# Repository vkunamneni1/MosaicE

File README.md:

# MosaicE
MosaicE is a PCB controller board that's powered by a XIAO RP2040, three buttons, a rotary encoder, and four LEDs. There are 3 modes: clock, binary counter, and gradient light mode. All modes are controlled by user input through the buttons and knob, and are all programmed in C++ (Arduino code).

## Modes
1. ***Clock*** - 1 LED blinks to acknowledge mode change. Then 3 LEDs act as an hour counter, minute counter, and second counter, all blinking when their counted time has elapsed.
2. ***Binary*** - 1 LED blinks to acknowledge mode change. Then the 4 LEDs act as a binary counter, counting up from 0000 to 1111. This repeats.
3. ***Gradient Light Mode*** - 1 LED blinks to acknowledge mode change. Then, the rotary encoder (knob) acts as a controller for all 4 LEDs. The more you turn it clockwise, the more LEDs that light up.
4. ***Stop*** - All LEDs blink to acknowledge that the stop button has been pressed. Essentially, it stops all mode functions.

## 3D Model

(models found on the GrabCAD Library and combined in KiCad)

## PCB Design

(made in KiCad)

## Schematic

(made in KiCad)

## Firmware
Source files can be found in the firmware directory. It was made in the Arduino IDE, using third-party libraries such as RotaryEncoder by Matthias Hertel.

##### made for Pathfinder

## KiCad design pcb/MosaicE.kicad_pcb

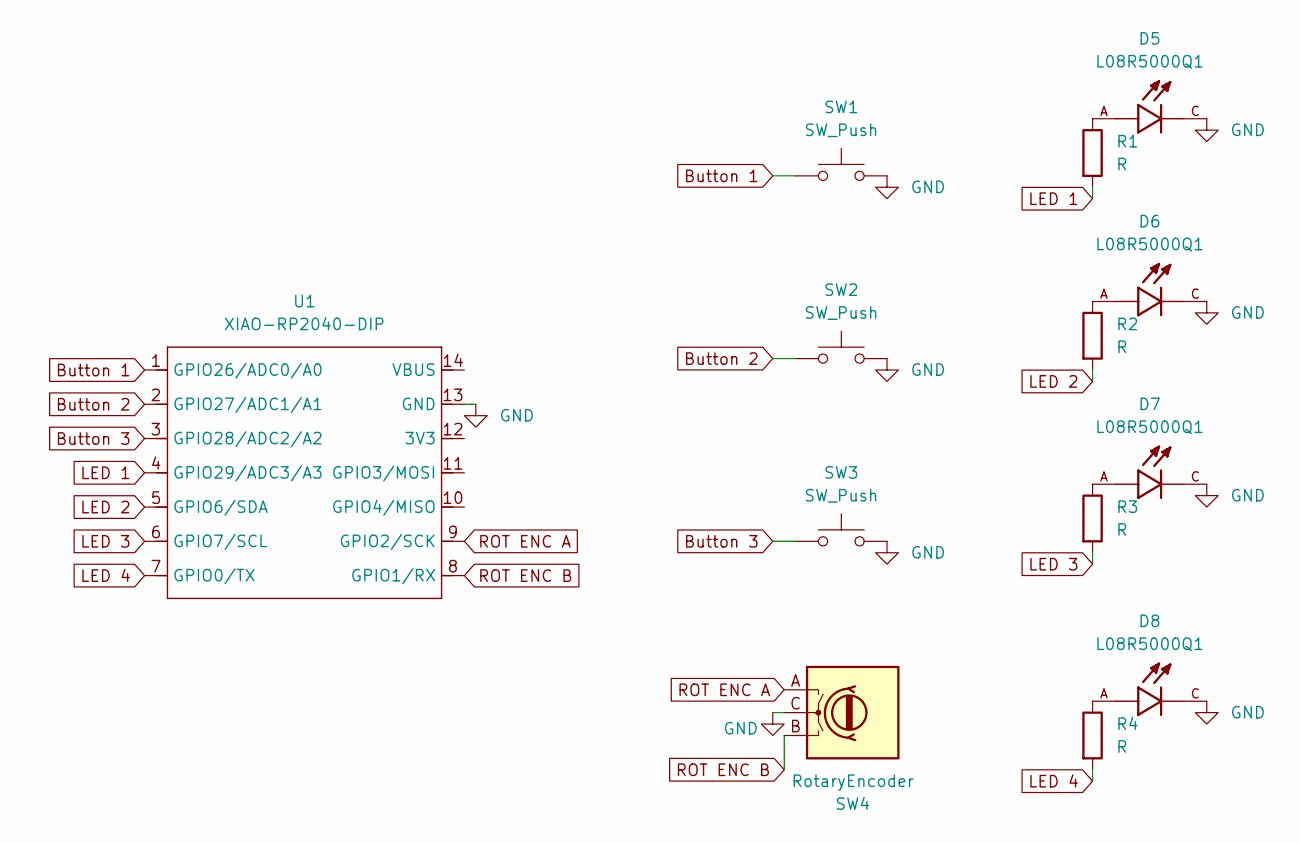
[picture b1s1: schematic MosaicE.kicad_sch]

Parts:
D5, D6, D7, D8: L08R5000Q1; LEDRD254W57D500H1070; PARTREV NA
R1, R2, R3, R4: R; R_Axial_DIN0204_L3.6mm_D1.6mm_P5.08mm_Horizontal
SW1, SW2, SW3: SW_Push; SW_Cherry_MX_1.00u_PCB
SW4: RotaryEncoder; RotaryEncoder_Alps_EC11E_Vertical_H20mm
U1: XIAO-RP2040-DIP

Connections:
Button 1: SW1.1, U1.1 (GPIO26/ADC0/A0)
Button 2: SW2.1, U1.2 (GPIO27/ADC1/A1)
Button 3: SW3.1, U1.3 (GPIO28/ADC2/A2)
GND: D5.C, D6.C, D7.C, D8.C, SW1.2, SW2.2, SW3.2, SW4.C, U1.13 (GND)
LED 1: R1.2, U1.4 (GPIO29/ADC3/A3)
LED 2: R2.2, U1.5 (GPIO6/SDA)
LED 3: R3.2, U1.6 (GPIO7/SCL)
LED 4: R4.2, U1.7 (GPIO0/TX)
unnamed: D5.A, R1.1
unnamed: D6.A, R2.1
unnamed: D7.A, R3.1
unnamed: D8.A, R4.1
ROT ENC A: SW4.A, U1.9 (GPIO2/SCK)
ROT ENC B: SW4.B, U1.8 (GPIO1/RX)

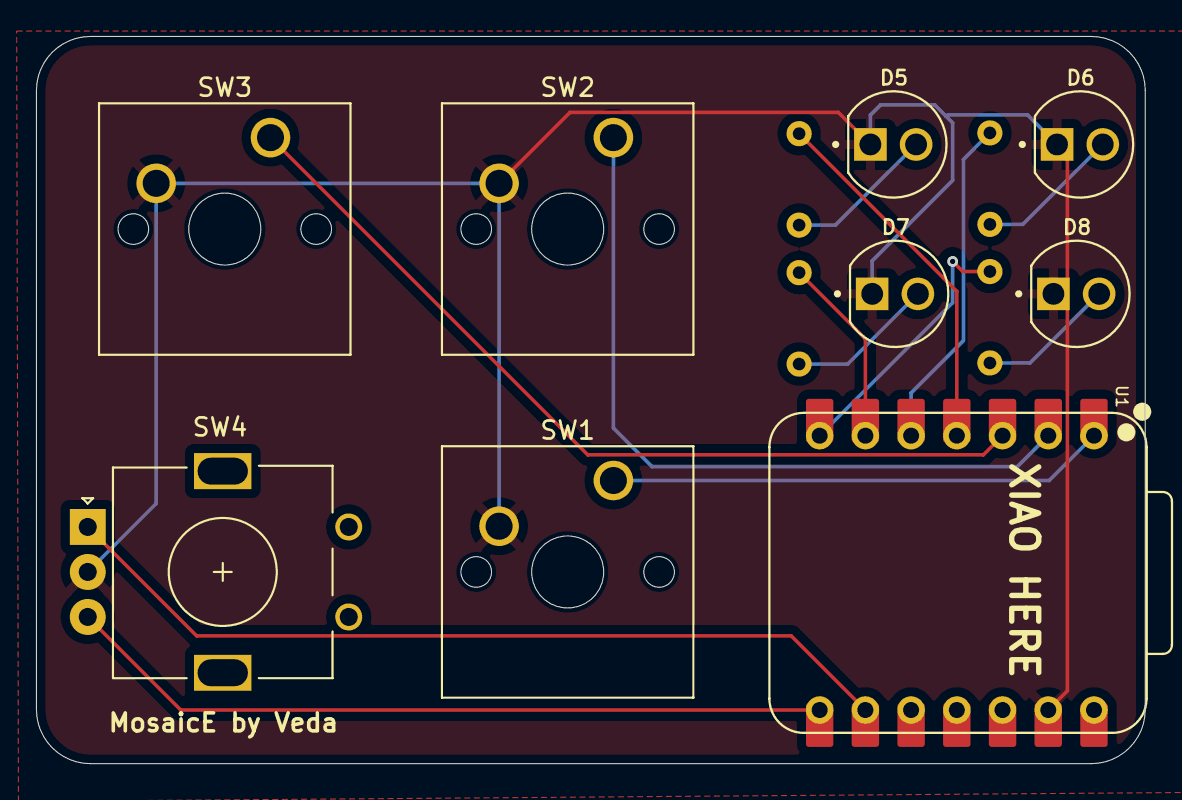
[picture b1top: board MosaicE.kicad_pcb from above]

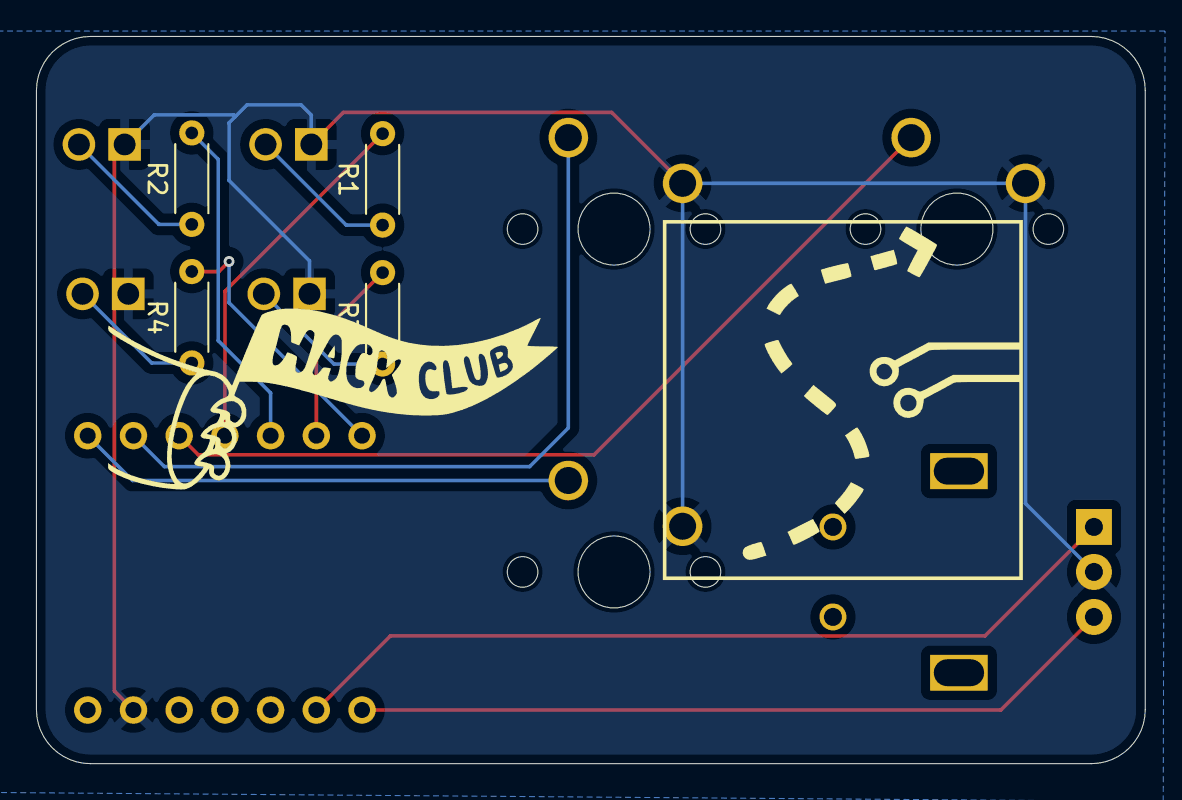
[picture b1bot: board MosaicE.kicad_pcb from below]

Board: 2 copper layers, 61.6 x 40.4 mm, 13 parts (4 on the bottom side), 14 nets.

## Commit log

2025-07-01 pcb done
2025-07-05 src files added
